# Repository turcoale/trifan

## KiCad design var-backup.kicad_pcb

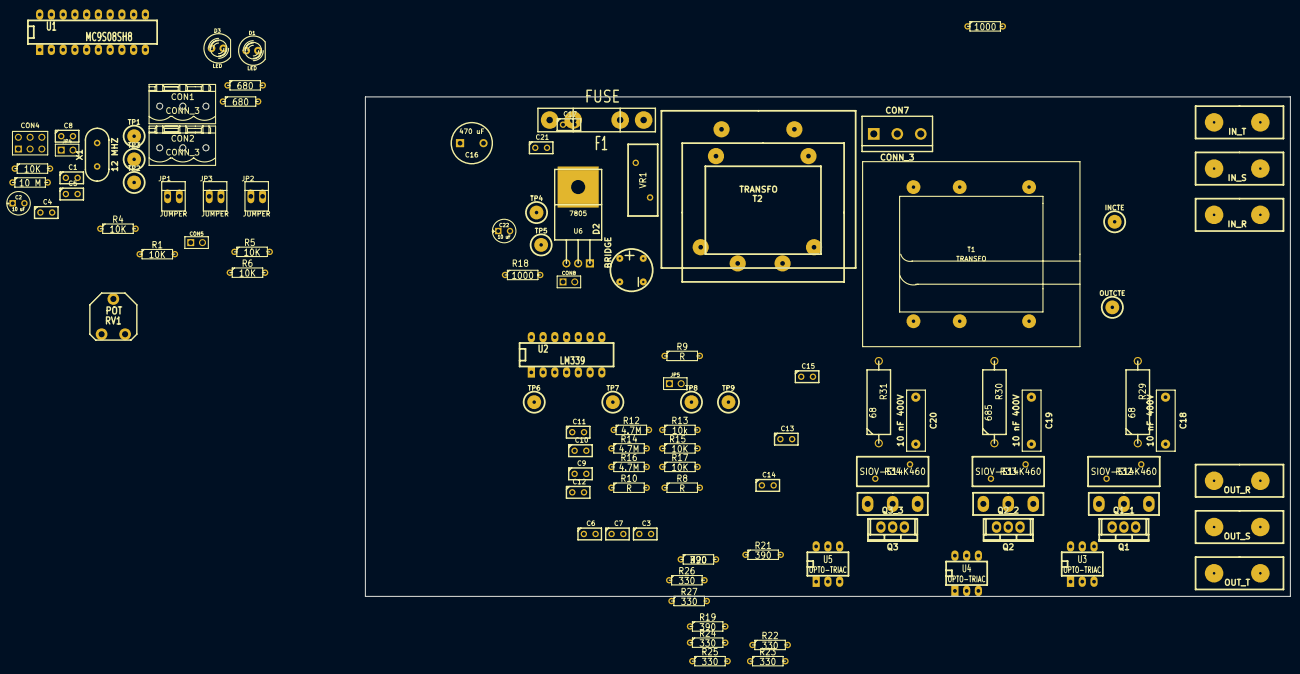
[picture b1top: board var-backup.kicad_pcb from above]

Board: 2 copper layers, 200.0 x 108.0 mm, 106 parts (0 on the bottom side), 53 nets, no tracks yet.

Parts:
C1, C5: 25 pF; C1
C2, C22: 10 uF; C1V5
C3, C7, C9: 0.1uF; C1
C4: 0,1 uF; C1
C6: C; C1
C8, C10, C11, C12, C13, C14, C15: C0.1 uF; C1
C16: 470 uF; C2V8
C17: 0.33 uF; C1
C18, C19, C20: 10 nF 400V; cnp_13x4mm
C21: 0.1 uF; C1
CON1, CON2: CONN_3; PHOENIX_MSTBA2,54-G_3
CON4: BDM; pin_array_3x2
CON5, CON8: CONN_2; PIN_ARRAY_2X1
CON7: CONN_3; bornier3
CON_40mm_1: OUT_R; CON_40mm_1
CON_40mm_1#2: OUT_S; CON_40mm_1
CON_40mm_1#3: OUT_T; CON_40mm_1
CON_40mm_1#4: IN_T; CON_40mm_1
CON_40mm_1#5: IN_R; CON_40mm_1
CON_40mm_1#6: IN_S; CON_40mm_1
D1, D3: LED; LED-5MM
D2: BRIDGE; Bridge-rond
F1: FUSE; FUSE5-20
INCTE: CONN_1; 1pin
JP1, JP2, JP3: JUMPER; PINHEAD1-2
JP4, JP5: JUMPER; PIN_ARRAY_2X1
OUTCTE: CONN_1; 1pin
Q1, Q2, Q3: TRIAC; TO-220
R1, R4, R5, R6, R7, R15, R17: 10K; R3
R2, R28: 680; R3
R3: 10 M; R3
R8, R9, R10: R; R3
R11, R18: 1000; R3
R12, R14, R16: 4.7M; R3
R13: 10k; R3
R19, R20, R21: 390; R3
R22, R23, R24, R25, R26, R27: 330; R3
R29, R31: 68; R7
R30: 685; R7
R32, R33, R34: SIOV-S14K460
RV1: POT; CVAR3X2
T1: TRANSFO; TRAFO_CTE_47x40
T2: TRANSFO; TF_34x42
TF30x35: VAL**; TF30x35
TOP3: Q1_1; TOP3
TOP3#2: Q2_2; TOP3
TOP3#3: Q3_3; TOP3
TP1, TP2, TP3, TP4, TP5, TP6, TP7, TP8, TP9: CONN_1; 1pin
U1: MC9S08SH8; DIP-20__300_ELL
U2: LM339; DIP-14__300_ELL
U3, U4, U5: OPTO-TRIAC; DIP-6__300_ELL
U6: 7805; TO220
VR1: VR; SIOV-S14K460
X1: 12 MHZ; HC-49V

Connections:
/BDM: CON4.1, U1.2
/EXTAL: C5.1, R3.2, U1.5, X1.2
/GM: CON5.1, R4.1, U1.8
/IC: R18.2, TP6.1, U1.20, U2.14
/In_R: CON_40mm_1#5.1, CON_40mm_1#5.2, INCTE.1, R12.1
/In_RT: OUTCTE.1, Q1.2, R29.1, R32.2, TOP3.2, U3.6
/In_S: CON_40mm_1#6.1, CON_40mm_1#6.2, F1.1, Q2.2, R14.1, R30.1, R33.2, T2.6, TF30x35.3, TOP3#2.2, U4.6
/In_T: CON7.1, CON_40mm_1#4.1, CON_40mm_1#4.2, Q3.2, R16.1, R31.1, R34.2, TOP3#3.2, U5.6
/Led1: D1.1, U1.7
/N: CON7.3, JP5.1, R13.2, R15.2, R17.2
/OPT1: C13.1, R19.2, TP1.1, U1.13
/OPT2: C14.1, R20.2, TP2.1, U1.12
/OPT3: C15.1, R21.2, TP3.1, U1.11
/RC: C11.1, R9.2, TP7.1, U1.17, U2.1
/RESET: C8.1, CON4.4, JP4.1, R7.2, U1.1
/RxD: CON1.2, U1.16
/SC: C10.1, R8.2, TP8.1, U1.18, U2.2
/TC: C12.1, R10.2, TP9.1, U1.14, U2.13
/TxD: CON1.3, U1.15
/XTAL: C1.1, R3.1, U1.6, X1.1
/c_Flash: JP2.1, R5.2, U1.10
/out_R: C18.2, CON_40mm_1.1, CON_40mm_1.2, Q1.1, R23.1, R32.1, TOP3.1
/out_S: C19.2, CON_40mm_1#2.1, CON_40mm_1#2.2, Q2.1, R25.1, R33.1, TOP3#2.1
/out_T: C20.2, CON_40mm_1#3.1, CON_40mm_1#3.2, Q3.1, R27.1, R34.1, TOP3#3.1
/select: JP3.1, R6.2, U1.19
/sensor: CON2.1, U1.9
/vreg: C2.1, C4.1, C6.1, C7.1, C9.1, C21.1, C22.1, CON2.3, CON4.6, CON8.1, R1.1, R4.2, R5.1, R6.1, R7.1, R8.1, R9.1, R10.1, R18.1, TP5.1, U1.3, U2.3, U6.1
GND: C1.2, C2.2, C3.2, C4.2, C5.2, C6.2, C7.2, C8.2, C9.2, C10.2, C11.2, C12.2, C13.2, C14.2, C15.2, C16.2, C17.2, C21.2, C22.2, CON1.1, CON2.2, CON4.2, CON5.2, CON8.2, D2.1, JP2.2, JP3.2, JP4.2, JP5.2, R2.1, R11.2, R28.2, RV1.3, T1.6, U1.4, U2.4, U2.6, U2.8, U2.10, U2.12, U3.2, U4.2, U5.2, U6.3
unnamed: C3.1, JP1.1, RV1.1, RV1.2
unnamed: C18.1, R29.2
unnamed: C20.1, R31.2
unnamed: R21.1, U5.1
unnamed: R20.1, U4.1
unnamed: C19.1, R30.2
unnamed: JP1.2, R1.2
unnamed: R22.2, R23.2, U3.4
unnamed: R12.2, R13.1, U2.7
unnamed: R14.2, R15.1, U2.5
unnamed: D2.4, T2.4, TF30x35.2
unnamed: D1.2, R2.2
unnamed: R19.1, U3.1
unnamed: D3.2, R28.1
unnamed: R16.2, R17.1, U2.11
unnamed: D2.2, T2.3, TF30x35.1
unnamed: F1.2, VR1.1
unnamed: Q2.3, R24.1, TOP3#2.3
unnamed: C16.1, C17.1, D2.3, D3.1, TP4.1, U6.2
unnamed: R24.2, R25.2, U4.4
unnamed: Q1.3, R22.1, TOP3.3
unnamed: R11.1, T1.5, U2.9
unnamed: CON7.2, T2.5, TF30x35.4, VR1.2
unnamed: Q3.3, R26.1, TOP3#3.3
unnamed: R26.2, R27.2, U5.4

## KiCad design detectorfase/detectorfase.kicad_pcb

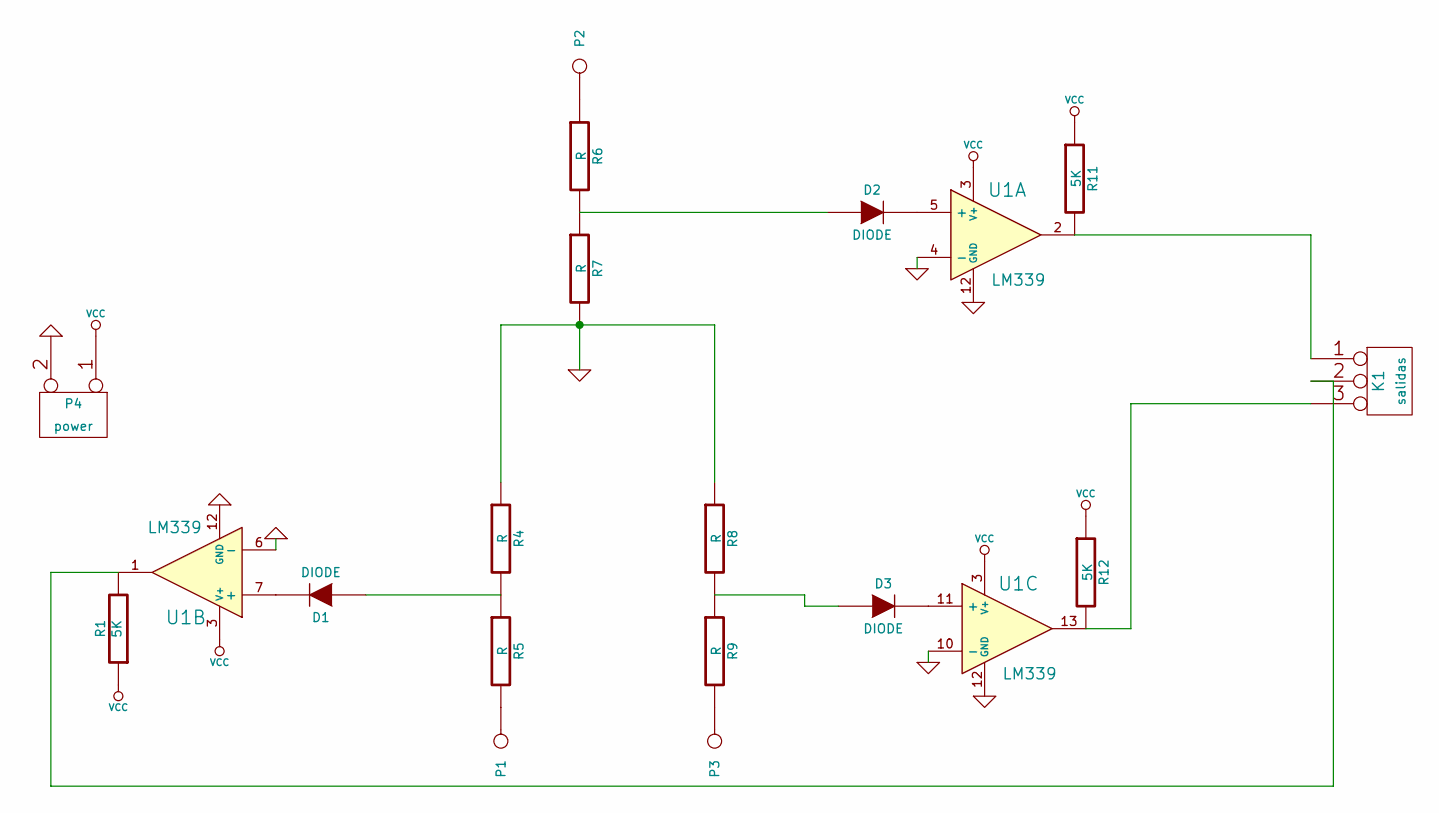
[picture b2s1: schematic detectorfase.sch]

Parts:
D1, D2, D3: DIODE
K1: salidas
P1: R
P2: T
P3: S
P4: power
R1, R11, R12: 5K
R4, R5, R6, R7, R8, R9: R
U1: LM339

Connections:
GND: P4.2 (PM), R4.1, R7.2, R8.1, U1.4 (-), U1.6 (-), U1.10 (-), U1.12 (GND)
unnamed: D1.2 (K), U1.7 (+)
unnamed: D3.1 (A), R8.2, R9.1
unnamed: D1.1 (A), R4.2, R5.1
unnamed: K1.1, R11.2, U1.2
unnamed: D2.1 (A), R6.2, R7.1
unnamed: K1.2 (PM), R1.2, U1.1
unnamed: K1.3, R12.2, U1.13
unnamed: D2.2 (K), U1.5 (+)
unnamed: P1.1, R5.2
unnamed: P3.1, R9.2
unnamed: P2.1, R6.1
unnamed: D3.2 (K), U1.11 (+)
VCC: P4.1, R1.1, R11.1, R12.1, U1.3 (V+)

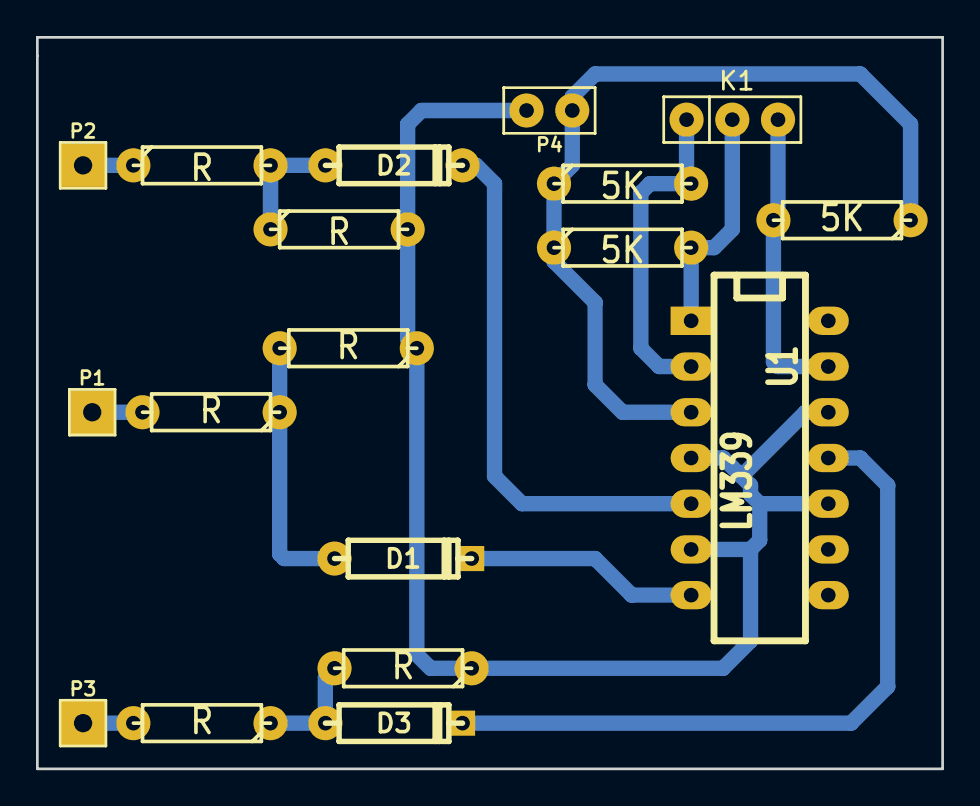
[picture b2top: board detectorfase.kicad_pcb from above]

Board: 2 copper layers, 50.3 x 40.6 mm, 18 parts (0 on the bottom side), 14 nets.

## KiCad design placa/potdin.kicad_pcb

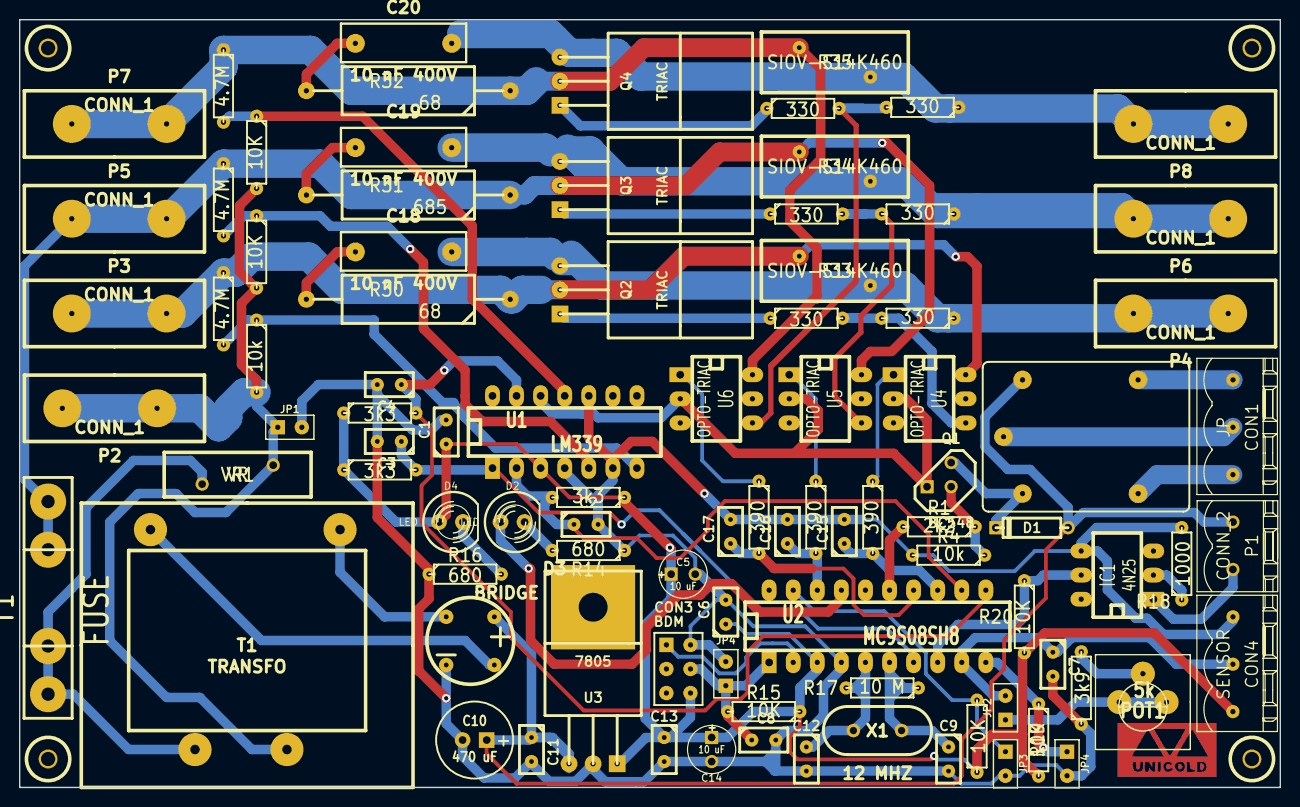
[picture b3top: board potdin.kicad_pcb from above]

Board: 2 copper layers, 133.0 x 81.0 mm, 96 parts (0 on the bottom side), 55 nets.

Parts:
C1, C7: 0.1uF; C1
C2, C3, C4: 10 nF; C1
C5, C14: 10 uF; C1V5
C6: 0,1 uF; C1
C8, C15, C16, C17: C0.1 uF; C1
C9, C12: 25 pF; C1
C10: 470 uF; C1V8
C11: 0.33 uF; C1
C13: 0.1 uF; C1
C18, C19, C20: 10 nF 400V; cnp_13x4mm
CON1: JP; PHOENIX_MSTBA2,54-G_3
CON3: BDM; pin_array_3x2
CON4: SENSOR; PHOENIX_MSTBA2,54-G_3
D1: 1N4148; D3
D2, D4: LED; LED-5MM
D3: BRIDGE; Bridge-rond
F1: FUSE; FUSE5-20
IC1: 4N25; DIP-6__300_ELL
JP1, JP2, JP3, JP4: JUMPER; PIN_ARRAY_2X1
JP4#2: C_FLASH; PIN_ARRAY_2X1
P1: CONN_2; PHOENIX_MSTBA2,54-G_2
P2, P3, P4, P5, P6, P7, P8: CONN_1; CON_40mm_1
POT1: 5k; CVAR3X2
Q1: BC548; TO92-123
Q2, Q3, Q4: TRIAC; TO220
R1: 2k2; R3
R2, R3, R5: 3k3; R3
R4, R7: 10k; R3
R6, R8, R10: 4.7M; R3
R9, R11, R13, R15, R19, R20: 10K; R3
R12: 3k9; R3
R14, R16: 680; R3
R17: 10 M; R3
R18: 1000; R3
R21, R22, R23: 390; R3
R24, R25, R26, R27, R28, R29: 330; R3
R30, R32: 68; RPOT
R31: 685; RPOT
R33, R34, R35: SIOV-S14K460
RL1: RM50-XX11; relay-JS-M
T1: TRANSFO; TF30x35
U1: LM339; DIP-14__300_ELL
U2: MC9S08SH8; DIP-20__300_ELL
U3: 7805; TO220
U4, U5, U6: OPTO-TRIAC; DIP-6__300_ELL
VR1: VR; SIOV-S14K230
X1: 12 MHZ; HC-49V
agu1, agu2, agu3, agu4: P***; 1pin

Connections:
/Alarma: R1.2, U2.15
/BDM: CON3.1, U2.2
/EXTAL: C12.1, R17.2, U2.5, X1.2
/GM: IC1.5, R20.1, U2.8
/In_R: P3.1, P3.2, Q2.3, R6.1, R30.1, R33.2, U4.6
/In_S: F1.1, P5.1, P5.2, Q3.3, R8.1, R31.1, R34.2, U5.6
/In_T: P7.1, P7.2, Q4.3, R10.1, R32.1, R35.2, U6.6
/Led1: D2.1, U2.17
/N: JP1.1, P2.1, P2.2, R7.2, R9.2, R11.2, T1.2, VR1.2
/OPT1: C15.1, R21.2, U2.13
/OPT2: C16.1, R22.2, U2.18
/OPT3: C17.1, R23.2, U2.14
/RC: C3.1, R3.2, U1.1, U2.7
/RESET: C8.1, CON3.4, JP4.1, R15.2, U2.1
/SC: C2.1, R2.2, U1.2, U2.12
/TC: C4.1, R5.2, U1.13, U2.11
/VO: C10.1, C11.1, D1.1, D3.3, P1.1, RL1.2, U3.2
/XTAL: C9.1, R17.1, U2.6, X1.1
/c_Flash: JP4#2.1, R19.1, U2.10
/out_R: C18.2, P4.1, P4.2, Q2.2, R25.1, R33.1
/out_S: C19.2, P6.1, P6.2, Q3.2, R27.1, R34.1
/out_T: C20.2, P8.1, P8.2, Q4.2, R29.1, R35.1
/select: JP3.1, R13.2, U2.19
/sensor: C7.1, CON4.2, JP2.2, U2.9
/vreg: C1.1, C5.1, C6.1, C13.1, C14.1, CON3.6, CON4.3, D4.1, R2.1, R3.1, R5.1, R13.1, R15.1, R19.2, R20.2, U1.3, U2.3, U3.1
GND: C1.2, C2.2, C3.2, C4.2, C5.2, C6.2, C7.2, C8.2, C9.2, C10.2, C11.2, C12.2, C13.2, C14.2, C15.2, C16.2, C17.2, CON3.2, CON4.1, D3.1, IC1.4, JP1.2, JP3.2, JP4.2, JP4#2.2, Q1.3, R4.2, R12.1, R14.1, R16.1, R18.2, U1.4, U1.6, U1.10, U1.12, U2.4, U3.3, U4.2, U5.2, U6.2
unnamed: C19.1, R31.2
unnamed: R8.2, R9.1, U1.5
unnamed: R24.2, R25.2, U4.4
unnamed: C18.1, R30.2
unnamed: R23.1, U6.1
unnamed: R22.1, U5.1
unnamed: D3.2, T1.4
unnamed: R21.1, U4.1
unnamed: F1.2, T1.1, VR1.1
unnamed: C20.1, R32.2
unnamed: POT1.1, R12.2
unnamed: JP2.1, POT1.2, POT1.3
unnamed: D4.2, R16.2
unnamed: D2.2, R14.2
unnamed: IC1.1, P1.2
unnamed: IC1.2, R18.1
unnamed: D3.4, T1.3
unnamed: R10.2, R11.1, U1.11
unnamed: CON1.1, RL1.NC
unnamed: CON1.3, RL1.NO
unnamed: D1.2, Q1.1, RL1.1
unnamed: CON1.2, RL1.C
unnamed: Q1.2, R1.1, R4.1
unnamed: R6.2, R7.1, U1.7
unnamed: Q2.1, R24.1
unnamed: Q4.1, R28.1
unnamed: R28.2, R29.2, U6.4
unnamed: Q3.1, R26.1
unnamed: R26.2, R27.2, U5.4

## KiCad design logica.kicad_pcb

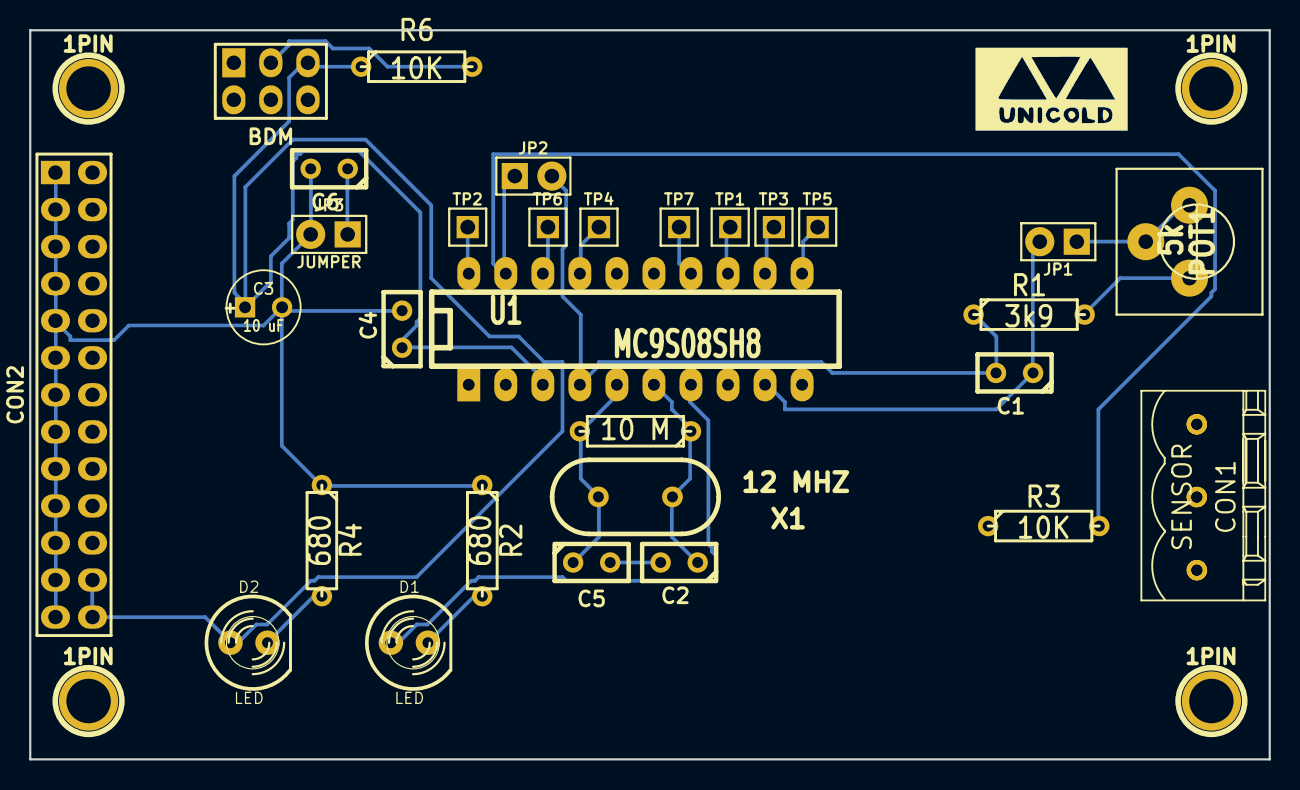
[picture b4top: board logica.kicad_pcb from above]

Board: 2 copper layers, 85.0 x 50.0 mm, 34 parts (0 on the bottom side), 24 nets.

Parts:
1PIN, 1PIN#2, 1PIN#3, 1PIN#4: P***; 1pin
C1: 0.1uF; C1
C2, C5: 25 pF; C1
C3: 10 uF; C1V5
C4: 0,1 uF; C1
C6: C0.1 uF; C1
CON1: SENSOR; PHOENIX_MSTBA2,54-G_3
CON2: CONN_13X2; pin_array_13x2
CON3: BDM; pin_array_3x2
D1, D2: LED; LED-5MM
JP1, JP2, JP3: JUMPER; PIN_ARRAY_2X1
POT1: 5k; CVAR3X2
R1: 3k9; R3
R2, R4: 680; R3
R3, R6: 10K; R3
R5: 10 M; R3
TP1, TP2, TP3, TP4, TP5, TP6, TP7: CONN_1; PIN_ARRAY_1
U1: MC9S08SH8; DIP-20__300_ELL
X1: 12 MHZ; HC-49V

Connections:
/Alarma: CON2.10, U1.15
/BDM: CON3.1, U1.2
/EXTAL: C5.1, R5.2, U1.5, X1.2
/GM: CON2.20, U1.8
/IC: CON2.2, TP2.1, U1.20
/Led1: D1.1, U1.7
/OPT1: CON2.18, TP1.1, U1.13
/OPT2: CON2.16, TP3.1, U1.12
/OPT3: CON2.14, TP5.1, U1.11
/RC: CON2.6, TP4.1, U1.17
/RESET: C6.1, CON3.4, JP3.1, R6.2, U1.1
/SC: CON2.4, TP6.1, U1.18
/TC: CON2.12, TP7.1, U1.14
/Temp: CON2.8, U1.16
/XTAL: C2.1, R5.1, U1.6, X1.1
/c_Flash: CON2.22, U1.10
/select: JP2.1, R3.2, U1.19
/sensor: C1.1, CON1.1, CON1.2, JP1.2, U1.9
/vreg: C3.1, C4.1, CON1.1, CON1.3, CON2.24, CON2.26, CON3.6, D2.1, R3.1, R6.1, U1.3
GND: C1.2, C2.2, C3.2, C4.2, C5.2, C6.2, CON1.1, CON2.1, CON2.3, CON2.5, CON2.7, CON2.9, CON2.11, CON2.13, CON2.15, CON2.17, CON2.19, CON2.21, CON2.23, CON2.25, CON3.2, JP2.2, JP3.2, R1.1, R2.1, R4.1, U1.4
unnamed: POT1.3, R1.2
unnamed: JP1.1, POT1.1, POT1.2
unnamed: D2.2, R4.2
unnamed: D1.2, R2.2

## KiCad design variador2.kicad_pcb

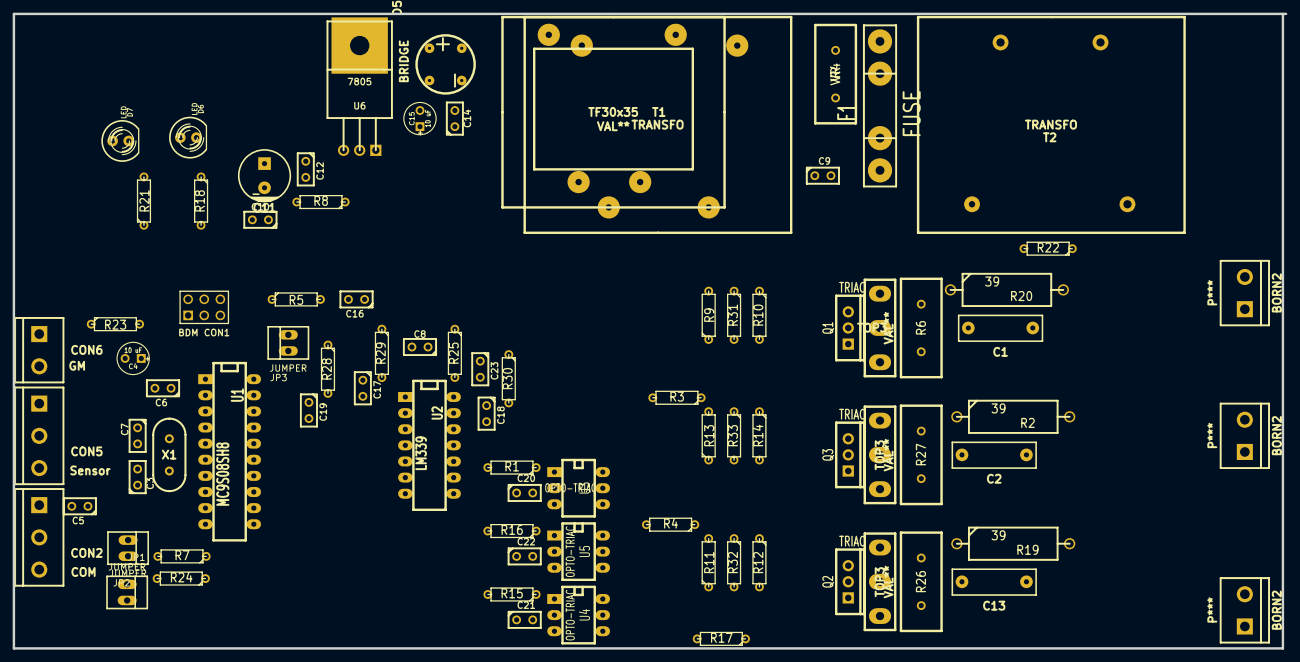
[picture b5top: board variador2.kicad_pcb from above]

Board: 2 copper layers, 200.5 x 100.0 mm, 87 parts (0 on the bottom side), 48 nets, no tracks yet.

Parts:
C1, C2, C13: 10 nF 400V; cnp_13x4mm
C3, C7: 25 pF; C1
C4, C15: 10 uF; C1V5
C5, C8: 0.1uF; C1
C6: 0,1 uF; C1
C9, C23: V***; C1
C10, C17, C18, C19, C20, C21, C22: C0.1 uF; C1
C11: 470 uF; CP_8x13mm
C12: 0.33 uF; C1
C14: 0.1 uF; C1
C16: C; C1
CON1: BDM; pin_array_3x2
CON2: COM; bornier3
CON5: Sensor; bornier3
CON6: GM; bornier2
D5: BRIDGE; Bridge-rond
D6, D7: LED; LED-5MM
F1: FUSE; FUSE5-20
JP1, JP2, JP3: JUMPER; PINHEAD1-2
P***: BORN2; bornier2
P***#2, P***#3: BORN2; bornier2
Q1, Q2, Q3: TRIAC; TO220_VERT
R1, R15, R16: 390; R3
R2, R19, R20: 39; R7
R3, R4, R17: 470; R3
R5, R7, R8, R12, R14, R23, R24: 10K; R3
R6, R26, R27: SIOV-S14K460
R9, R11, R13: 4.7M; R3
R10, R31, R32, R33: 10k; R3
R18, R21: 680; R3
R22: 1000; R3
R25, R28, R29, R30: R; R3
T1, T2: TRANSFO; TF_34x42
TF30x35: VAL**; TF30x35
TOP3, TOP3#2, TOP3#3: VAL**; TOP3
U1: MC9S08SH8; DIP-20__300_ELL
U2: LM339; DIP-14__300_ELL
U3, U4, U5: OPTO-TRIAC; DIP-6__300_ELL
U6: 7805; TO220
VR4: VR; SIOV-S14K460
X1: 12 MHZ; HC-49V

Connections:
/BDM: CON1.1, U1.2
/EXTAL: C7.1, U1.5, X1.2
/GM: CON6.1, R23.1, U1.8
/IC: C23.1, R25.2, U1.20, U2.14
/In_R: F1.1, P***#2.2, T2.6
/In_RT: Q1.2, R6.2, R9.1, R20.1, T2.5, TOP3#3.2, U3.6
/In_S: P***.2, Q2.2, R11.1, R19.1, R26.2, TOP3#2.2, U4.6
/In_T: P***#3.2, Q3.2, R2.1, R13.1, R27.2, TOP3.1, U5.6
/Led1: D7.1, U1.7
/N: R10.2, R12.2, R14.2, VR4.2
/OPT1: C20.1, R1.2, U1.13
/OPT2: C22.1, R16.2, U1.12
/OPT3: C21.1, R15.2, U1.11
/RC: C17.1, R29.2, U1.17, U2.2
/RESET: C10.1, CON1.4, R8.2, U1.1
/RxD: CON2.2, U1.16
/SC: C19.1, R28.2, U1.18, U2.1
/TC: C18.1, R30.2, U1.14, U2.13
/TxD: CON2.3, U1.15
/XTAL: C3.1, U1.6, X1.1
/c_Flash: JP1.1, R24.2, U1.10
/out_R: C1.2, P***#2.1, Q1.3, R3.2, R6.1, TOP3#3.3, U3.4
/out_S: C13.2, P***.1, Q2.3, R17.2, R26.1, TOP3#2.3, U4.4
/out_T: C2.2, P***#3.1, Q3.3, R4.2, R27.1, TOP3.3, U5.4
/select: JP3.1, R5.2, U1.19
/sensor: C5.1, CON5.1, JP2.1, U1.9
/vreg: C4.1, C6.1, C8.1, C14.1, C15.1, C16.1, CON1.6, CON5.3, R5.1, R7.1, R8.1, R23.2, R24.1, R25.1, R28.1, R29.1, R30.1, U1.3, U2.12, U6.1
GND: C3.2, C4.2, C5.2, C6.2, C7.2, C8.2, C10.2, C11.2, C12.2, C14.2, C15.2, C16.2, C17.2, C18.2, C19.2, C20.2, C21.2, C22.2, C23.2, CON1.2, CON2.1, CON5.2, CON6.2, D5.1, JP1.2, JP3.2, R18.2, R21.1, R22.2, R31.2, R32.2, R33.2, T2.3, U1.4, U2.3, U2.5, U2.7, U2.8, U2.11, U3.2, U4.2, U5.2, U6.3
unnamed: C1.1, R20.2
unnamed: C13.1, R19.2
unnamed: C2.1, R2.2
unnamed: R11.2, R12.1, R32.1, U2.6
unnamed: D6.2, R18.1
unnamed: D7.2, R21.2
unnamed: R1.1, U3.1
unnamed: R9.2, R10.1, R31.1, U2.4
unnamed: F1.2, VR4.1
unnamed: Q1.1, R3.1, TOP3#3.1
unnamed: R13.2, R14.1, R33.1, U2.10
unnamed: R16.1, U5.1
unnamed: R15.1, U4.1
unnamed: JP2.2, R7.2
unnamed: D5.4, T1.4
unnamed: D5.2, T1.3
unnamed: Q2.1, R17.1, TOP3#2.1
unnamed: C11.1, C12.1, D5.3, D6.1, U6.2
unnamed: R22.1, T2.4, U2.9
unnamed: Q3.1, R4.1, TOP3.2

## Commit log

2016-02-16 commit inicial
2016-02-16 agregadas graficas
2016-02-22 backup
2016-02-29 ultimo commit febrero
